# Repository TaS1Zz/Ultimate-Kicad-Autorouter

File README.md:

# Ultimate Kicad Autorouter

Автотрассировщик печатных плат KiCad: октолинейный A* (трассы только под 0/45/90°) с согласованием перегрузки
(PathFinder), шинами, дифпарами, шириной трасс по току и проверкой результата DRC самого KiCad.

*An octilinear (0/45/90°) autorouter for 4-layer KiCad boards: PathFinder negotiated congestion, bus lanes,
impedance-matched differential pairs, current-based track widths, power polygons with IR-drop analysis,
and a KiCad DRC feedback loop.*

**Документация:** [возможности](docs/features.md) · [установка и запуск](docs/usage.md) ·
[конфигурация](docs/configuration.md) · [как это работает](docs/algorithms.md) · [плагин KiCad](docs/plugin.md) ·
[разработка](docs/development.md)

## Быстрый старт

Нужны Python 3.10+ (`pip install -r requirements.txt`) и, для проверки DRC, KiCad 8+ (`kicad-cli`).

```bash
build.bat                                          # ядро A* (Windows; Linux/macOS — build.sh)
python route_board.py boards/demo.toml out/demo    # трассировка → плата → DRC KiCad → отчёт
```

Результат: `out/demo_routed.kicad_pcb` (зоны залиты KiCad), `out/demo_report.md` и `.json`.
Без C-компилятора: `pip install ziglang`, затем `build.bat` — он сам найдёт GCC, Clang, MSVC или zig.

## Тестовая плата

`example/demo_board.kicad_pcb` собирается скриптом `tools/make_demo_board.py` только из стандартных библиотек
KiCad (запуск — Python из комплекта KiCad). 100 × 70 мм, 4 слоя, 47 футпринтов, 36 цепей:
MCU в LQFP-48, драйвер светодиодов в QFN-32 с открытой площадкой, USB-C с дифпарой D+/D−, LDO 3,3 В,
матрица кнопок 2 × 4 с диодами, шина из 8 светодиодов, разъём питания/SWD.

Результат на ней (`out/demo_report.md`):

| | |
|---|---|
| Неразведено | 0 |
| Нарушений зазоров / обрывов (своя проверка) | 0 / 0 |
| DRC KiCad по трассировке | 2 замечания `starved_thermal` (терморазгрузка у GND-выводов); ещё одно — шелкография |
| Отрезков не под 0/45/90° | 0 |
| Отрезков / переходов | 271 / 71 |
| Обход (длина трассы / минимальное дерево) | 1,03 |
| Дифпара USB: Zdiff / перекос длин | 90 Ом / 0,1 мм (0,6 пс) |
| Падение напряжения VBUS по меди (1,31 А) | 37 мВ — 0,74 % |
| Время | ~55 с трассировка + ~15 с DRC |

## Как это работает

Порядок — от самых ограниченных цепей к самым свободным:

1. **Fanout и переходы под площадками.** Переходы под открытыми GND-площадками микросхем ставятся сеткой.
   Выводы GND и питания у микросхем с шагом ≤ 0,5 мм выводятся на переходы. Глубина перехода выбирается
   по загрузке: дальше от переходов соседей, чтобы между ними остался канал под трассу.
   Режим `fanout.mode = "all"` выводит на переходы все выводы (для плотных BGA/QFN).
2. **Дифпары.** Ширина и зазор подбираются под целевой Zdiff по стеку (`impedance.py`, IPC-2141).
   Пара идёт только по слою с опорной плоскостью. Второй проводник притягивается к первому на шаге w + s.
   После разводки длины проводников выравниваются: на прямом или диагональном участке короткого проводника
   вставляется «змейка» в сторону от напарника, каждый её отрезок проверяется на зазоры.
3. **Питание.** Ширина считается отдельно для каждого слоя по двум условиям: нагрев по IPC-2221 и падение
   напряжения 2 %. Цепи от 1 А дополнительно получают полигон вдоль трассы, его заливает KiCad.
4. **GND.** Каждая GND-площадка получает свой короткий широкий отвод на плоскость, переход ставится
   как можно ближе.
5. **Сигналы — PathFinder.** На время согласования цепи «мягкие»: могут перекрываться, но платят за чужую
   территорию. Цена растёт с каждым проходом, в местах конфликтов копится история, и цепи расходятся сами,
   без зависимости от порядка. Остаток конфликтов добивает точная проверка геометрии и rip-up.
6. **Постобработка.** Спрямление (1–2 отрезка 0/45/90° вместо «ступенек»), точный вход в центр площадки,
   слияние коллинеарных и перекрывающихся отрезков, обрезка висящих хвостов. Каждое действие принимается
   только при сохранении связности.
7. **DRC KiCad в цикле.** `kicad-cli` заливает зоны и проверяет плату. Замечания, которые исправляются
   трассировкой (терморазгрузка, зазоры, висящие трассы, обрывы), исправляются, и проверка повторяется.
   Сохраняется лучший вариант.
8. **Отчёт.** Качество (углы, изломы, обходы, параллельность шин), падение напряжения по реальной меди
   после заливки (сетка сопротивлений, решается методом конечных разностей) и длины проводников дифпар.

### Шины и матрицы

* **Топология цепи** — минимальное остовное дерево от вывода ведущей микросхемы: строки и столбцы матрицы
  идут цепочкой от элемента к элементу, без «звёзд».
* **Группы шин** определяются по именам (`COL0..3`, `ROW0..1`, `LED_K0..7`, …). Цепи группы разводятся подряд
  в порядке выводов микросхемы, и каждая притягивается к полосе на шаге «ширина + зазор» от соседей.
* **Коридоры выхода.** Перед каждым выводом микросхемы с мелким шагом зарезервирована короткая полоса.
  Чужие цепи могут пройти через неё, но платят за это, поэтому дифпара или питание, разведённые первыми,
  не замуровывают выводы соседей.

### Правила

Все числа берутся из платы и конфига, в коде их нет:
* контур — из `Edge.Cuts`;
* сетка трассировки 0,1 мм выравнивается по центрам выводов с мелким шагом;
* толщина меди — из стека платы, по умолчанию JLC04161H-7628;
* зазоры, ширины и переходы — из `.kicad_pro`;
* токи, источники и потребители питания, быстрые цепи и дифпары — из `boards/*.toml`.

Быстрые цепи ведутся только по слою, у которого ближайший слой меди — плоскость. В стеке 7628
у In2 до плоскости In1 1,065 мм, а до сигнального B — 0,21 мм, поэтому для быстрых цепей годится только F.Cu.
У своих площадок им разрешён короткий переход на другой слой (например, перескок D+ через D− под USB-C).

Принципы — сплошная земля, короткие широкие отводы на неё, широкое короткое питание, опорная плоскость
у быстрых сигналов — общепринятые, их же излагают Хоровиц и Хилл в «Искусстве схемотехники».
Числа взяты из IPC-2221, IPC-2141 и удельного сопротивления меди.

## Плагин для KiCad

```bash
python tools/install_kicad_plugin.py
```

Команда кладёт в папку плагинов KiCad загрузчик со ссылкой на этот репозиторий. В редакторе плат появляется
кнопка «Ultimate Kicad Autorouter». По нажатию плагин:
1. сохраняет плату;
2. запускает трассировку во внешнем Python: в Python KiCad нет numpy/shapely/scipy, поэтому путь к нужному
   Python задаётся переменной `UKA_PYTHON`, иначе берётся `python` из PATH;
3. переносит в открытую плату трассы, переходы и полигоны питания и заливает зоны.

Конфиг берётся из `<плата>.toml` рядом с платой, если он есть, иначе используются настройки по умолчанию.
Работает в KiCad 8–10 (Action-плагин pcbnew).

## Тесты

```bash
python -m pytest -q
```

24 теста:
* **правила:** IPC-2221, импеданс, слои быстрых цепей;
* **ядро A\*:** прямой путь, обход, «нет пути», переход между слоями, карта цены;
* **постобработка;**
* **тестовая плата:** полная разводка с порогами качества;
* **KiCad:** DRC и плагин, если KiCad установлен.

GitHub Actions прогоняет всё, кроме KiCad-тестов, на Linux и Windows.

## Своя плата

Скопируйте `boards/demo.toml`, укажите в нём свою плату и задайте:
* `power.currents` / `power.loads` — токи. От них зависят ширины, полигоны и расчёт падения напряжения;
* `power.sources` — откуда втекает ток;
* `nets.fast`, `nets.diff_pairs` — быстрые цепи и пары с целевым импедансом;
* `fanout` — разъёмы, выводы которых тоже надо вывести на переходы.

Параметры поиска (`route2.py`: цены изломов и переходов, полосы, PathFinder) переопределяются без правки кода:
`set ROUTER_VIAC=80` перед запуском.

## Файлы

| Файл | Что делает |
|---|---|
| `route_board.py` | Полный цикл по конфигу платы. |
| `route2.py` | Маршрутизатор: поиск, PathFinder, шины, пары, fanout, коридоры выхода, спрямление, rip-up. |
| `astar.c` | Ядро поиска: октолинейный A* (слой, y, x, направление), карты цены клеток и переходов, проверка достижимости, буферы на поток. |
| `rules.py`, `config.py`, `impedance.py` | Правила, конфиг и автоопределение, расчёт импеданса. |
| `pipeline.py`, `power.py`, `diffpair.py` | Запись платы, полигоны и падение напряжения, DRC KiCad в цикле, отчёт, длины пар. |
| `merge.py`, `post.py`, `zones.py` | Постобработка с проверкой связности, заливки GND на внешних слоях. |
| `check.py`, `metrics.py`, `viz.py` | Проверка зазоров и связности, метрики качества, картинка. |
| `tools/make_demo_board.py` | Генератор тестовой платы. |
| `kicad_plugin/`, `tools/install_kicad_plugin.py` | Плагин для редактора плат KiCad и его установка. |
| `tests/`, `.github/workflows/ci.yml` | Тесты и CI. |

## Ограничения и что в работе

* Проводники дифпары у концов (разъём, микросхема) расходятся по разным путям; связанный участок
  занимает не всю длину. Длины выравниваются, но импеданс на расходящихся участках не контролируется.
* PathFinder на плотных шинах сходится не до нуля: последние 3–4 конфликта добивает точный rip-up.
* Параллельная разводка (`--threads`) ускоряет только большие платы с непересекающимися окнами цепей:
  на тестовой плате выигрыша почти нет.
* Плагин проверен без интерфейса (Python KiCad 10 + `kicad-cli`); кнопку в живом редакторе стоит
  проверить на своей установке.
* `starved_thermal` у GND-выводов, зажатых сигнальными, может остаться: это правится расстановкой
  или правилом зоны.
* Сетка 0,1 мм: шаги выводов не кратные 0,05 мм выравниваются хуже.

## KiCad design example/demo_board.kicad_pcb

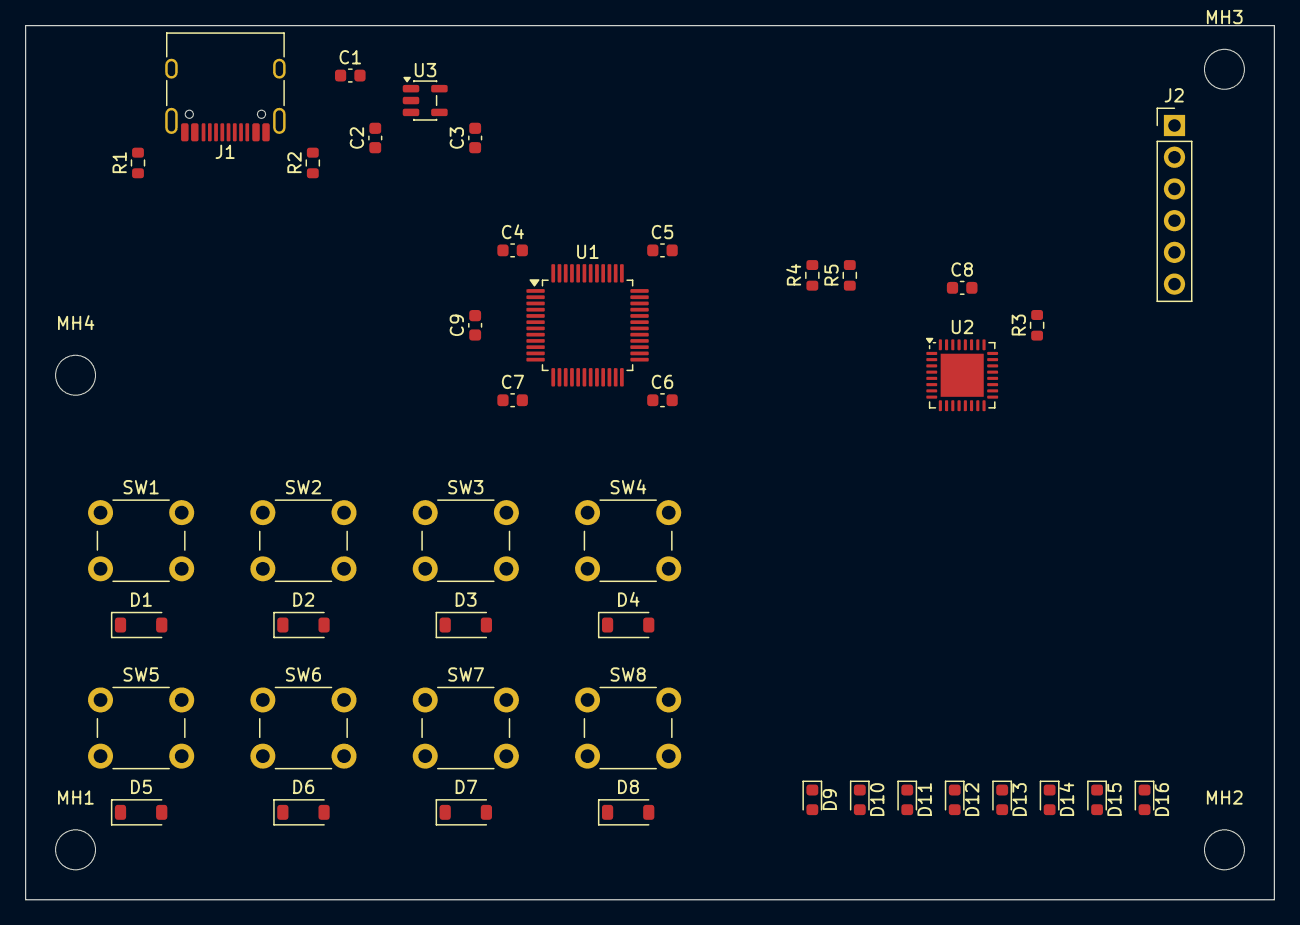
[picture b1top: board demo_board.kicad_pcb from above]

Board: 4 copper layers, 100.0 x 70.0 mm, 47 parts (0 on the bottom side), 36 nets, no tracks yet.

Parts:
C1: 10u; C_0603_1608Metric
C2, C3, C8: 1u; C_0603_1608Metric
C4, C5, C6, C7, C9: 100n; C_0603_1608Metric
D1, D2, D3, D4, D5, D6, D7, D8: 1N4148W; D_SOD-123
D9, D10, D11, D12, D13, D14, D15, D16: LED; LED_0603_1608Metric
J1: USB-C; USB_C_Receptacle_HRO_TYPE-C-31-M-12
J2: PWR/SWD; PinHeader_1x06_P2.54mm_Vertical
MH1, MH2, MH3, MH4: MountingHole_3.2mm_M3
R1, R2: 5.1k; R_0603_1608Metric
R3: 10k; R_0603_1608Metric
R4, R5: 4.7k; R_0603_1608Metric
SW1, SW2, SW3, SW4, SW5, SW6, SW7, SW8: SW; SW_PUSH_6mm
U1: MCU; LQFP-48_7x7mm_P0.5mm
U2: LED driver; QFN-32-1EP_5x5mm_P0.5mm_EP3.45x3.45mm
U3: LDO 3V3; SOT-23-5

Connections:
+3V3: C3.1, C4.1, C5.1, C6.1, C7.1, J2.1, R4.1, R5.1, U1.1, U1.9, U1.24, U1.36, U1.48, U3.5
CC1: J1.A5, R1.1
CC2: J1.B5, R2.1
COL0: SW1.1, SW5.1, U1.12
COL1: SW2.1, SW6.1, U1.13
COL2: SW3.1, SW7.1, U1.14
COL3: SW4.1, SW8.1, U1.15
GND: C1.2, C2.2, C3.2, C4.2, C5.2, C6.2, C7.2, C8.2, C9.2, J1.A1, J1.A12, J1.B1, J1.B12, J1.SH, J2.5, R1.2, R2.2, R3.2, U1.8, U1.23, U1.35, U1.47, U2.26, U2.33, U3.2
I2C_SCL: R4.2, U1.42, U2.2
I2C_SDA: R5.2, U1.43, U2.3
LED_EN: U1.44, U2.4
LED_ISET: R3.1, U2.27
LED_K0: D9.1, U2.9
LED_K1: D10.1, U2.10
LED_K2: D11.1, U2.11
LED_K3: D12.1, U2.12
LED_K4: D13.1, U2.13
LED_K5: D14.1, U2.14
LED_K6: D15.1, U2.15
LED_K7: D16.1, U2.16
NRST: C9.1, J2.4, U1.7
unnamed: D1.2, SW1.2
unnamed: D2.2, SW2.2
unnamed: D3.2, SW3.2
unnamed: D4.2, SW4.2
unnamed: D5.2, SW5.2
unnamed: D6.2, SW6.2
unnamed: D7.2, SW7.2
unnamed: D8.2, SW8.2
ROW0: D1.1, D2.1, D3.1, D4.1, U1.10
ROW1: D5.1, D6.1, D7.1, D8.1, U1.11
SWCLK: J2.3, U1.37
SWDIO: J2.2, U1.34
USB_D+: J1.A6, J1.B6, U1.33
USB_D-: J1.A7, J1.B7, U1.32
VBUS: C1.1, C2.1, C8.1, D9.2, D10.2, D11.2, D12.2, D13.2, D14.2, D15.2, D16.2, J1.A4, J1.A9, J1.B4, J1.B9, J2.6, U2.25, U3.1, U3.3
